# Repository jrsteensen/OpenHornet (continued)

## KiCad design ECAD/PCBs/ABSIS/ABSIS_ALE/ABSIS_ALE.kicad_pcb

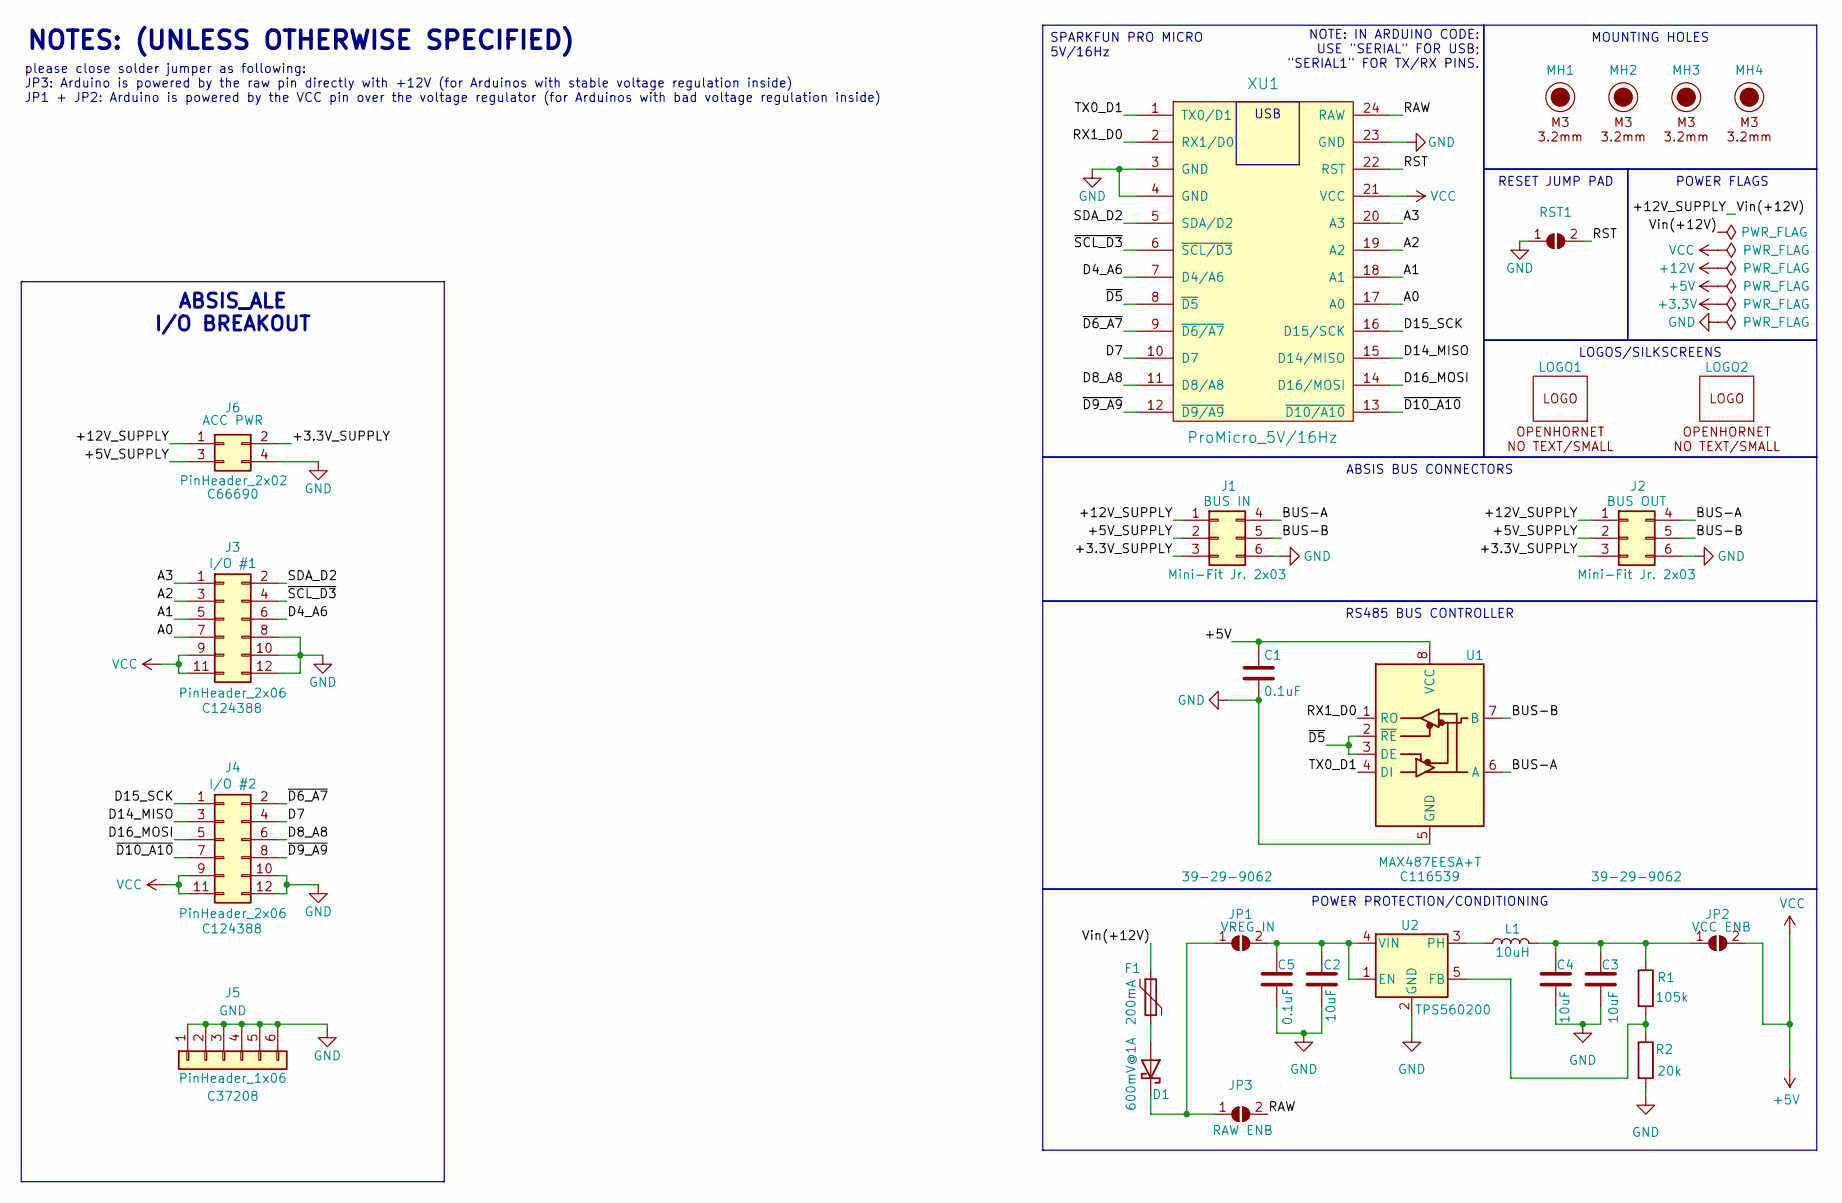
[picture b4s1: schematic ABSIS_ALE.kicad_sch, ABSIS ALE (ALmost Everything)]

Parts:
C1: 0.1uF; C_0805_2012Metric; Manufacturer PN CC0805KRX7R9BB104; LCSC C14663
C2, C3: 10uF; C_0805_2012Metric; Manufacturer PN CL21A106KAYNNNE; LCSC C15850
C4: 10uF; C_0805_2012Metric; Manufacturer PN CC0603KRX5R6BB105; LCSC C15850
C5: 0.1uF; C_0805_2012Metric; Manufacturer PN CC0603KRX7R9BB104; LCSC C14663
D1: 600mV@1A; D_SOD-323_HandSoldering; Manufacturer PN 1N5819WS; LCSC C191023
F1: 200mA; Fuse_0805_2012Metric; Manufacturer PN 0805L020/15XR; LCSC C7472558
J1, J2: Mini-Fit Jr. 2x03; Molex_Mini-Fit_Jr_5566-06A2_2x03_P4.20mm_Vertical; Manufacturer PN 39-29-9062; LCSC C505177
J3, J4: PinHeader_2x06; PinHeader_2x06_P2.54mm_Vertical; Manufacturer PN B-2100S12P-B110; LCSC C124388
J5: PinHeader_1x06; PinHeader_1x06_P2.54mm_Vertical; Manufacturer PN PH1-06-UA; LCSC C37208
J6: PinHeader_2x02; PinHeader_2x02_P2.54mm_Vertical; Manufacturer PN C66690; LCSC C66690
JP1: VREG IN; SolderJumper-2_P1.3mm_Open_RoundedPad1.0x1.5mm
JP2: VCC ENB; SolderJumper-2_P1.3mm_Open_RoundedPad1.0x1.5mm
JP3: RAW ENB; SolderJumper-2_P1.3mm_Open_RoundedPad1.0x1.5mm
L1: 10uH; L_0603_1608Metric; LCSC C86083
LOGO1, LOGO2: LOGO; LOGO_OH_NoText_Small
MH1, MH2, MH3, MH4: M3 / 3.2mm; MountingHole_3.2mm_M3_DIN965
R1: 105k; R_0603_1608Metric; LCSC C141685
R2: 20k; R_0603_1608Metric; LCSC C105575
RST1: RST; SolderJumper-2_P1.3mm_Open_RoundedPad1.0x1.5mm
U1: MAX487EESA+T; SOIC-8_3.9x4.9mm_P1.27mm; Manufacturer PN MAX487EESA+T; LCSC C116539
U2: TPS560200; SOT-23-5; LCSC C83671
XU1: ProMicro_5V/16Hz; DIP-24_W15.24mm_Socket; Manufacturer PN Pro Micro - 5V/16MHz

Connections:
+5V: C1.1, J3.9, J3.11, J4.9, J4.11, JP2.2 (B), U1.8 (VCC), XU1.21 (VCC)
/+3.3V_SUPPLY: J1.3, J2.3, J6.2
/+5V_SUPPLY: J1.2, J2.2, J6.3
/+12V_SUPPLY: F1.1, J1.1, J2.1, J6.1
/A0: J3.7, XU1.17 (A0)
/A1: J3.5, XU1.18 (A1)
/A2: J3.3, XU1.19 (A2)
/A3: J3.1, XU1.20 (A3)
/BUS-A: J1.4, J2.4, U1.6 (A)
/BUS-B: J1.5, J2.5, U1.7 (B)
/D4_A6: J3.6, XU1.7 (D4/A6)
/D7: J4.4, XU1.10 (D7)
/D8_A8: J4.6, XU1.11 (D8/A8)
/D14_MISO: J4.3, XU1.15 (D14/MISO)
/D15_SCK: J4.1, XU1.16 (D15/SCK)
/D16_MOSI: J4.5, XU1.14 (D16/MOSI)
/RAW: JP3.2 (B), XU1.24 (RAW)
/RST: RST1.2 (B), XU1.22 (RST)
/RX1_D0: U1.1 (RO), XU1.2 (RX1/D0)
/SDA_D2: J3.2, XU1.5 (SDA/D2)
/TX0_D1: U1.4 (DI), XU1.1 (TX0/D1)
/~D5: U1.2 (~RE), U1.3 (DE), XU1.8 (~D5)
/~D6_A7: J4.2, XU1.9 (~D6/A7)
/~D9_A9: J4.8, XU1.12 (~D9/A9)
/~D10_A10: J4.7, XU1.13 (~D10/A10)
/~SCL_D3: J3.4, XU1.6 (~SCL/D3)
GND: C1.2, C2.2, C3.2, C4.2, C5.2, J1.6, J2.6, J3.8, J3.10, J3.12, J4.10, J4.12, J5.1, J5.2, J5.3, J5.4, J5.5, J5.6, J6.4, R2.2, RST1.1 (A), U1.5 (GND), U2.2 (GND), XU1.3 (GND), XU1.4 (GND), XU1.23 (GND)
unnamed: D1.2 (A), F1.2
unnamed: D1.1 (K), JP1.1 (A), JP3.1 (A)
unnamed: C2.1, C5.1, JP1.2 (B), U2.1 (EN), U2.4 (VIN)
unnamed: C3.1, C4.1, JP2.1 (A), L1.2, R1.1
unnamed: R1.2, R2.1, U2.5 (FB)
unnamed: L1.1, U2.3 (PH)

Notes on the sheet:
NOTES: (UNLESS OTHERWISE SPECIFIED)
NOTE: IN ARDUINO CODE: USE "SERIAL" FOR USB; "SERIAL1" FOR TX/RX PINS.
please close solder jumper as following: JP3: Arduino is powered by the raw pin directly with +12V (for Arduinos with stable voltage regulation inside) JP1 + JP2: Arduino is powered by the VCC pin over the voltage regulator (for Arduinos with bad voltage regulation inside)
SPARKFUN PRO MICRO 5V/16Hz
LOGOS/SILKSCREENS
USB
RS485 BUS CONTROLLER
POWER PROTECTION/CONDITIONING
POWER FLAGS
ABSIS_ALE I/O BREAKOUT
MOUNTING HOLES
RESET JUMP PAD
ABSIS BUS CONNECTORS

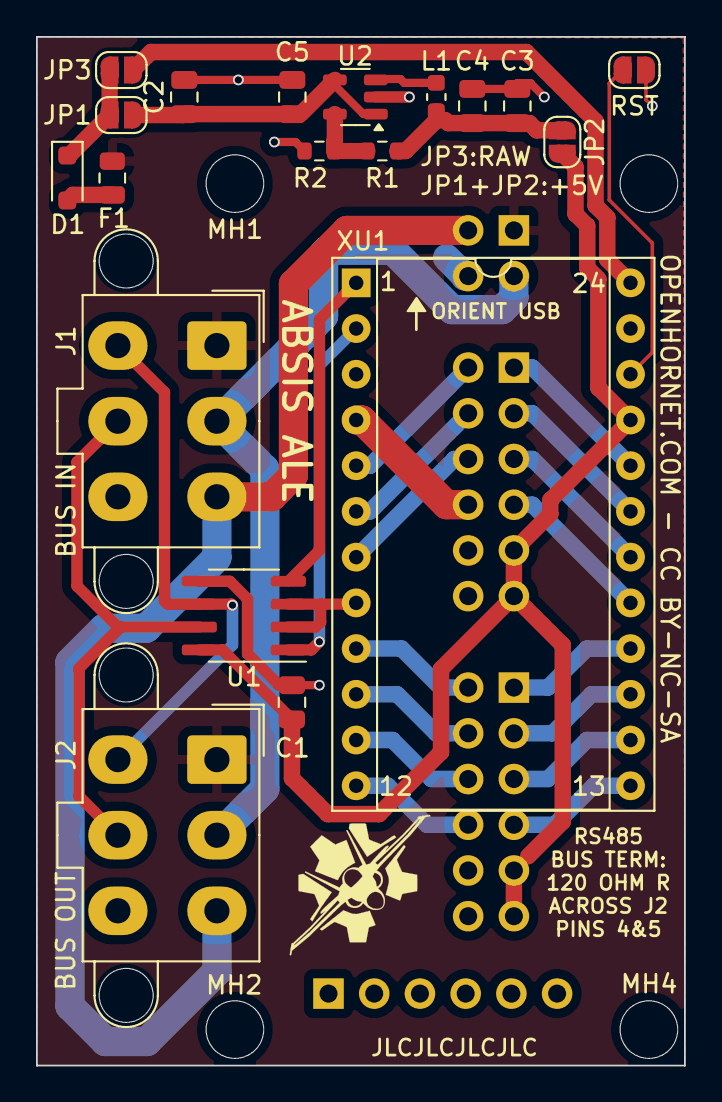
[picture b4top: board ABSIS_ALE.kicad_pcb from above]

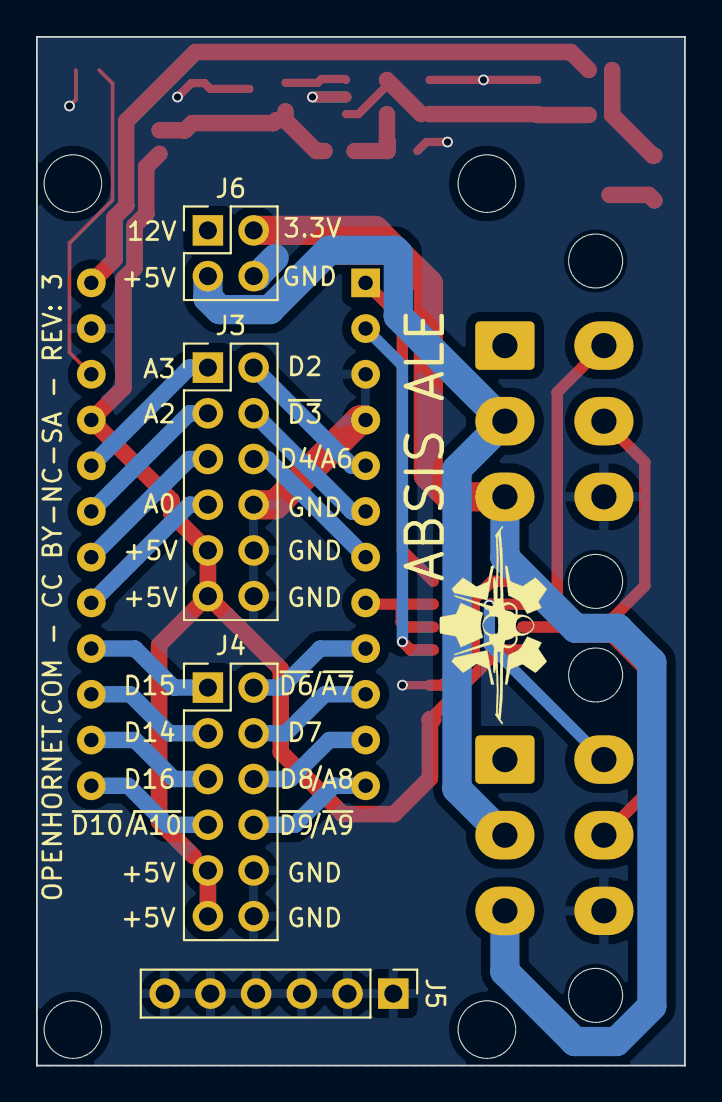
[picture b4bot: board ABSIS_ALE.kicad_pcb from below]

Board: 2 copper layers, 36.0 x 57.2 mm, 29 parts (5 on the bottom side), 33 nets.

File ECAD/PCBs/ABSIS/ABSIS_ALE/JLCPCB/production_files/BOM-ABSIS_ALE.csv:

"Reference","Value","Datasheet","Footprint","Qty","DNP","LCSC"
"C1,C5","0.1uF","https://datasheet.lcsc.com/szlcsc/YAGEO-CChttps://datasheet.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","OH_Footprints:C_0805_2012Metric","2","","C5120075"
"C2,C3,C4","10uF","https://datasheet.lcsc.com/szlcsc/Samsung-Electro-Mechanics-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","OH_Footprints:C_0805_2012Metric","3","","C15850"
"D1","600mV@1A","https://www.lcsc.com/datasheet/lcsc_datasheet_2204281430_Gua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","Diode_SMD:D_SOD-323_HandSoldering","1","","C191023"
"F1","200mA","https://wmsc.lcsc.com/wmsc/upload/file/pdf/v2/lcsc/240103172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","Fuse:Fuse_0805_2012Metric","1","","C7472558"
"J1,J2","Mini-Fit Jr. 2x03","https://datasheet.lcsc.com/lcsc/2005291105_MOLEX-39299062_C5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","OH_Footprints:Molex_Mini-Fit_Jr_5566-06A2_2x03_P4.20mm_Vertical","2","","C505177"
"J3,J4","PinHeader_2x06","https://datasheet.lcsc.com/lcsc/1810241611_Ckmtw-Shenzhen-Ca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","OH_Footprints:PinHeader_2x06_P2.54mm_Vertical","2","","C124388"
"J5","PinHeader_1x06","https://datasheet.lcsc.com/lcsc/1810312320_BOOMELE-Boom-Prec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","OH_Footprints:PinHeader_1x06_P2.54mm_Vertical","1","","C37208"
"J6","PinHeader_2x02","https://jlcpcb.com/partdetail/boomele_boom_Precision_elec-C6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","OH_Footprints:PinHeader_2x02_P2.54mm_Vertical","1","","C66690"
"L1","10uH","https://www.lcsc.com/datasheet/lcsc_datasheet_2410121333_Mur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","Inductor_SMD:L_0603_1608Metric","1","","C86083"
"R1","105k","https://www.lcsc.com/datasheet/C98220.pdf","Resistor_SMD:R_0603_1608Metric","1","","C141685"
"R2","20k","https://www.lcsc.com/datasheet/C98220.pdf","Resistor_SMD:R_0603_1608Metric","1","","C105575"
"U1","MAX487EESA+T","https://datasheet.lcsc.com/szlcsc/Maxim-Integrated-MAX487EES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","OH_Footprints:SOIC-8_3.9x4.9mm_P1.27mm","1","","C116539"
"U2","TPS560200","http://www.ti.com/lit/ds/symlink/tps560200.pdf","Package_TO_SOT_SMD:SOT-23-5","1","","C83671"
"XU1","ProMicro_5V/16Hz","https://cdn.sparkfun.com/datasheets/Dev/Arduino/Boards/ATMeg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","OH_Footprints:DIP-24_W15.24mm_Socket","1","",""

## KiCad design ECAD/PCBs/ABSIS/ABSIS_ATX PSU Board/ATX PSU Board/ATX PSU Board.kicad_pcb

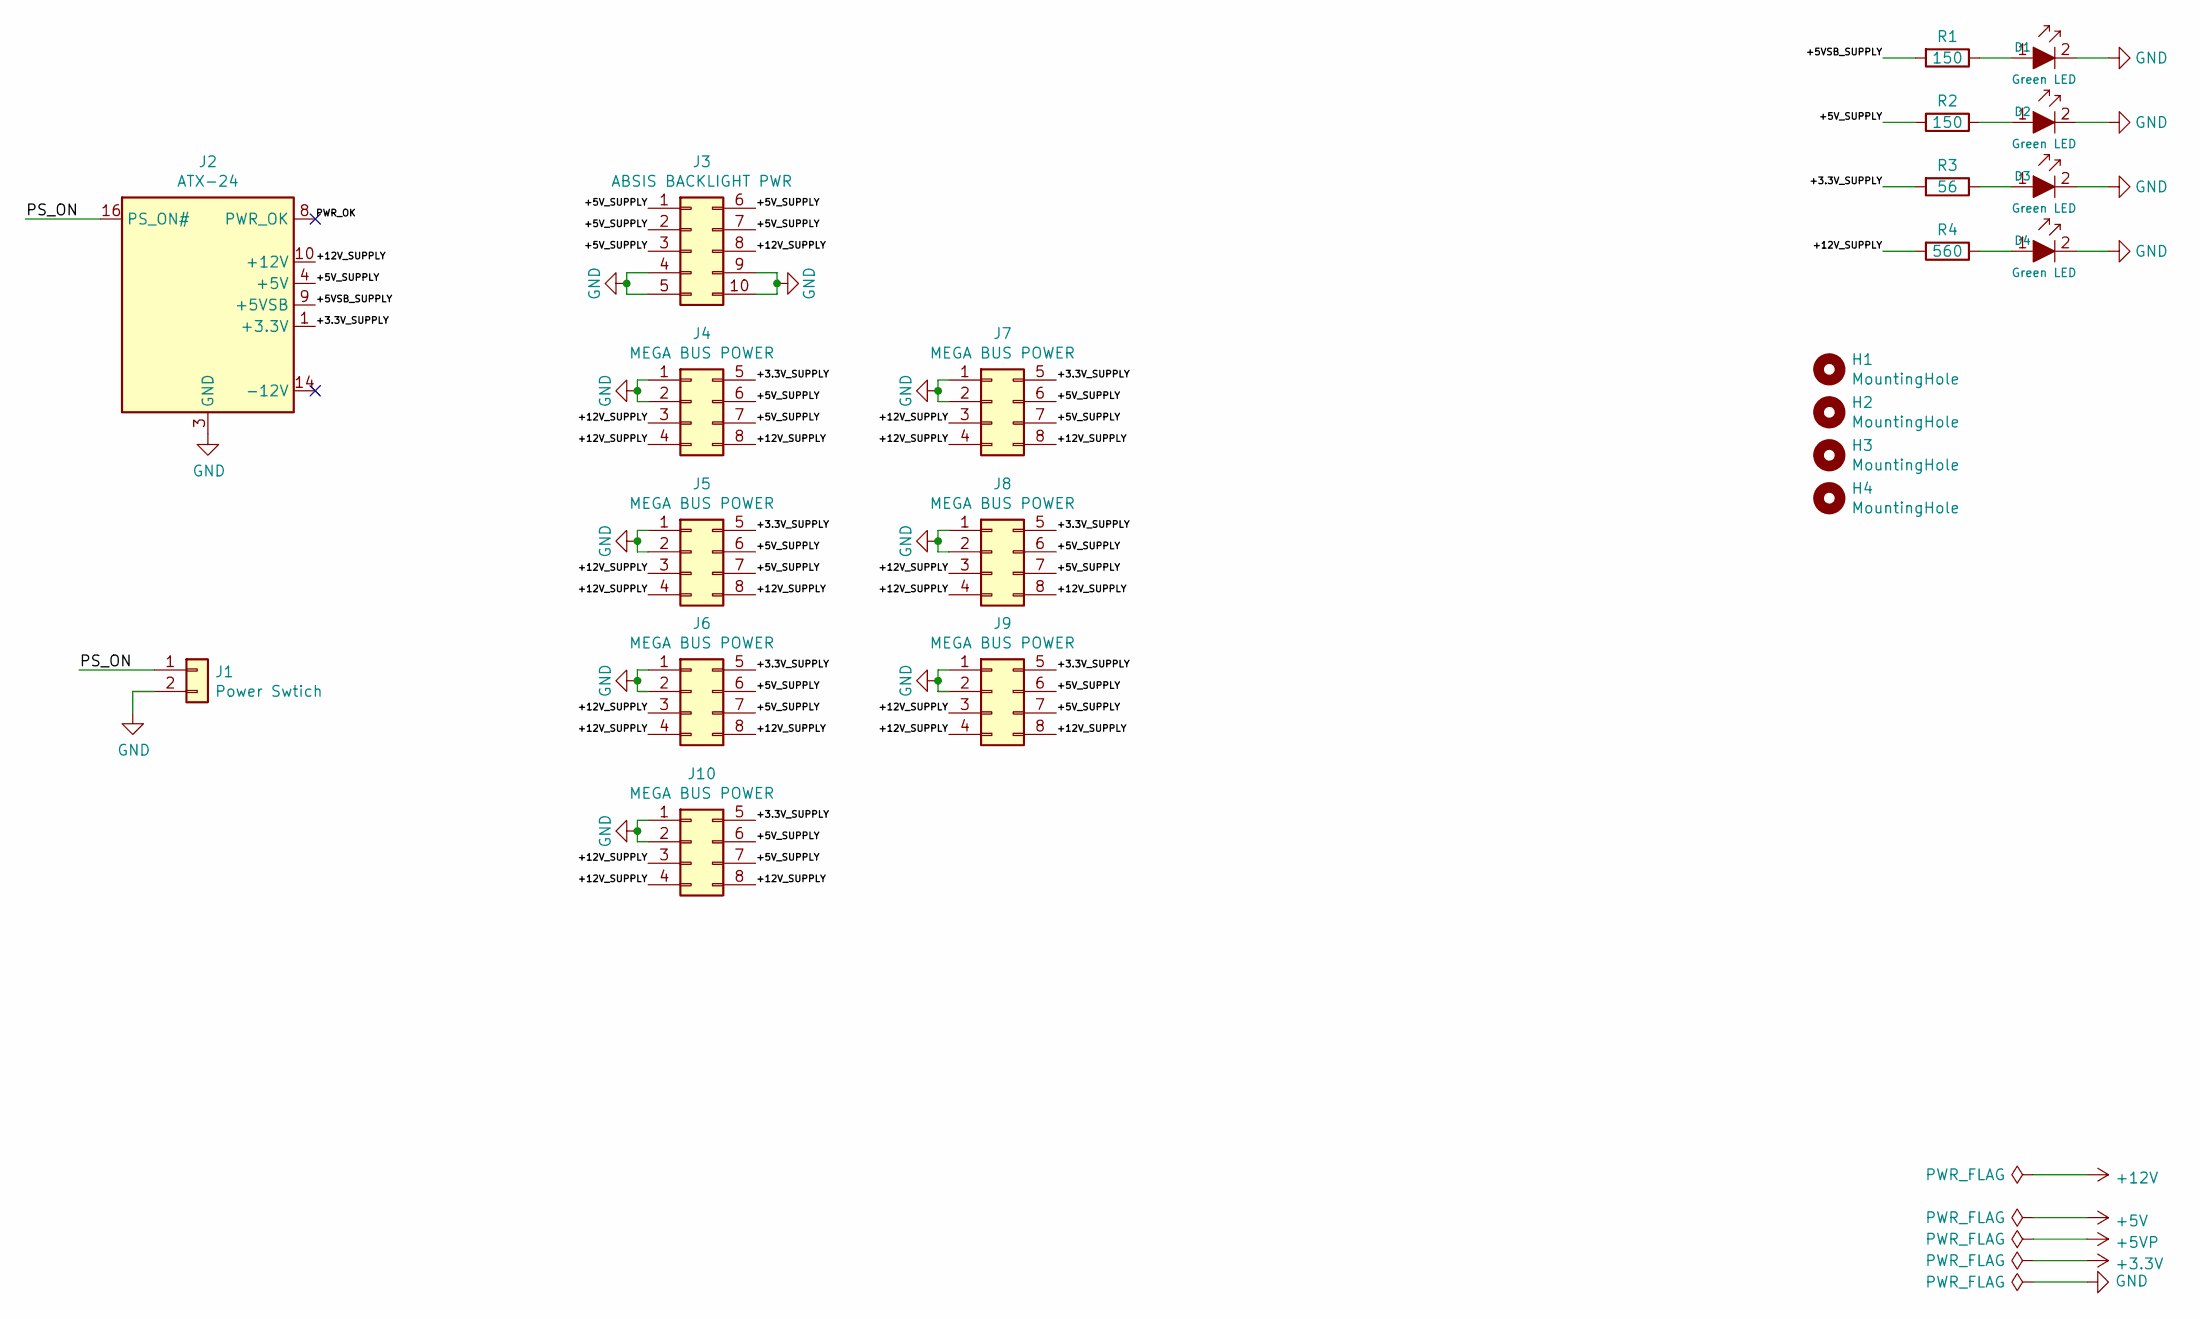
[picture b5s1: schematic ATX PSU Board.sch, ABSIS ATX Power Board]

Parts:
D1, D2, D3, D4: Green LED; LED_0805_2012Metric_Pad1.15x1.40mm_HandSolder; MPN LG R971-KN-1; Digi-Key_PN 475-1410-1-ND
H1, H2, H3, H4: MountingHole; Arduino_1pin
J1: Power Swtich; Molex_Micro-Fit_3.0_43045-0212_2x01_P3.00mm_Vertical
J2: ATX-24; Molex_Mini-Fit_Jr_5566-24A2_2x12_P4.20mm_Vertical
J3: ABSIS BACKLIGHT PWR; Molex_Mini-Fit_Jr_5566-10A2_2x05_P4.20mm_Vertical
J4, J5, J6, J7, J8, J9, J10: MEGA BUS POWER; Molex_Mini-Fit_Jr_5566-08A2_2x04_P4.20mm_Vertical
R1, R2: 150; R_0805_2012Metric_Pad1.20x1.40mm_HandSolder
R3: 56; R_0805_2012Metric_Pad1.20x1.40mm_HandSolder
R4: 560; R_0805_2012Metric_Pad1.20x1.40mm_HandSolder

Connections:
/+3.3V_SUPPLY: J2.1 (+3.3V), J2.2 (+3.3V), J2.12 (+3.3V), J2.13 (+3.3V), J4.5, J5.5, J6.5, J7.5, J8.5, J9.5, J10.5, R3.2
/+5VSB_SUPPLY: J2.9 (+5VSB), R1.2
/+5V_SUPPLY: J2.4 (+5V), J2.6 (+5V), J2.21 (+5V), J2.22 (+5V), J2.23 (+5V), J3.1, J3.2, J3.3, J3.6, J3.7, J4.6, J4.7, J5.6, J5.7, J6.6, J6.7, J7.6, J7.7, J8.6, J8.7, J9.6, J9.7, J10.6, J10.7, R2.2
/+12V_SUPPLY: J2.10 (+12V), J2.11 (+12V), J3.8, J4.3, J4.4, J4.8, J5.3, J5.4, J5.8, J6.3, J6.4, J6.8, J7.3, J7.4, J7.8, J8.3, J8.4, J8.8, J9.3, J9.4, J9.8, J10.3, J10.4, J10.8, R4.2
/PS_ON: J1.1, J2.16 (PS_ON#)
/PWR_OK: J2.8 (PWR_OK)
GND: D1.2, D2.2, D3.2, D4.2, J1.2, J2.3 (GND), J2.5 (GND), J2.7 (GND), J2.15 (GND), J2.17 (GND), J2.18 (GND), J2.19 (GND), J2.24 (GND), J3.4, J3.5, J3.9, J3.10, J4.1, J4.2, J5.1, J5.2, J6.1, J6.2, J7.1, J7.2, J8.1, J8.2, J9.1, J9.2, J10.1, J10.2
unnamed: D1.1, R1.1
unnamed: D2.1, R2.1
unnamed: D3.1, R3.1
unnamed: D4.1, R4.1

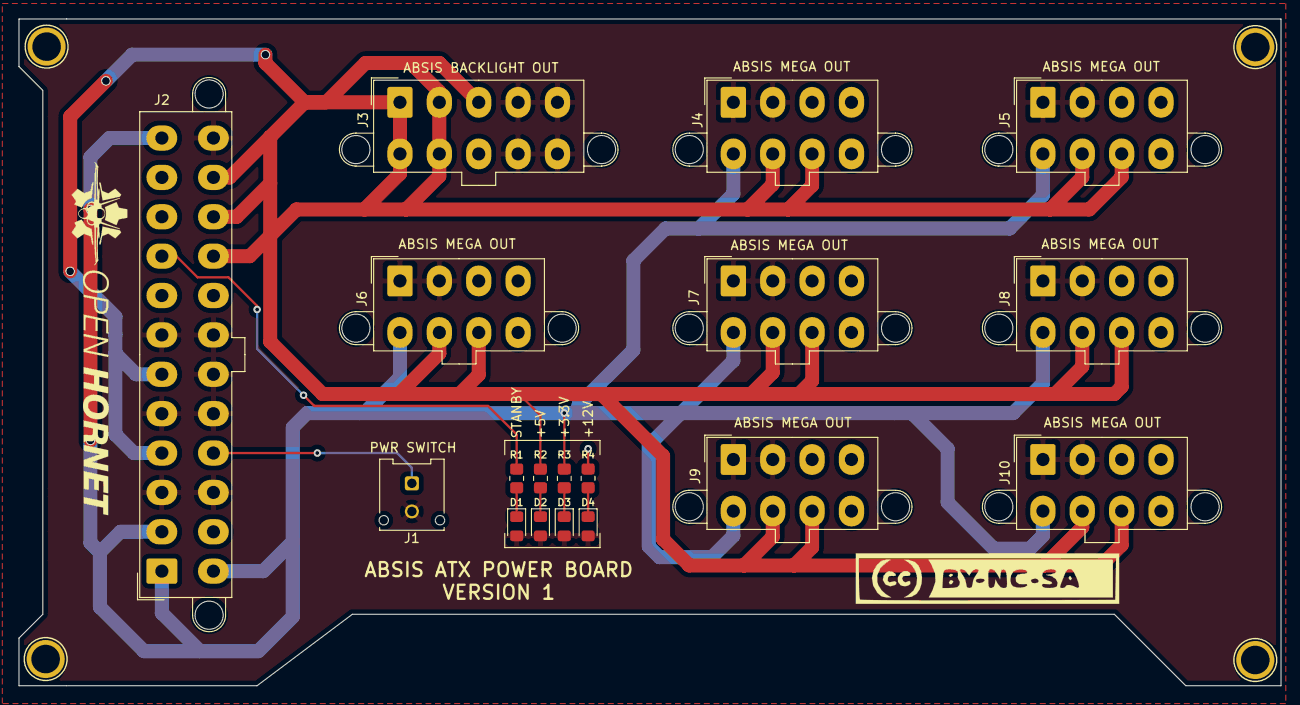
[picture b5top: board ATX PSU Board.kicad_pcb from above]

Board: 2 copper layers, 134.6 x 71.1 mm, 22 parts (0 on the bottom side), 10 nets.

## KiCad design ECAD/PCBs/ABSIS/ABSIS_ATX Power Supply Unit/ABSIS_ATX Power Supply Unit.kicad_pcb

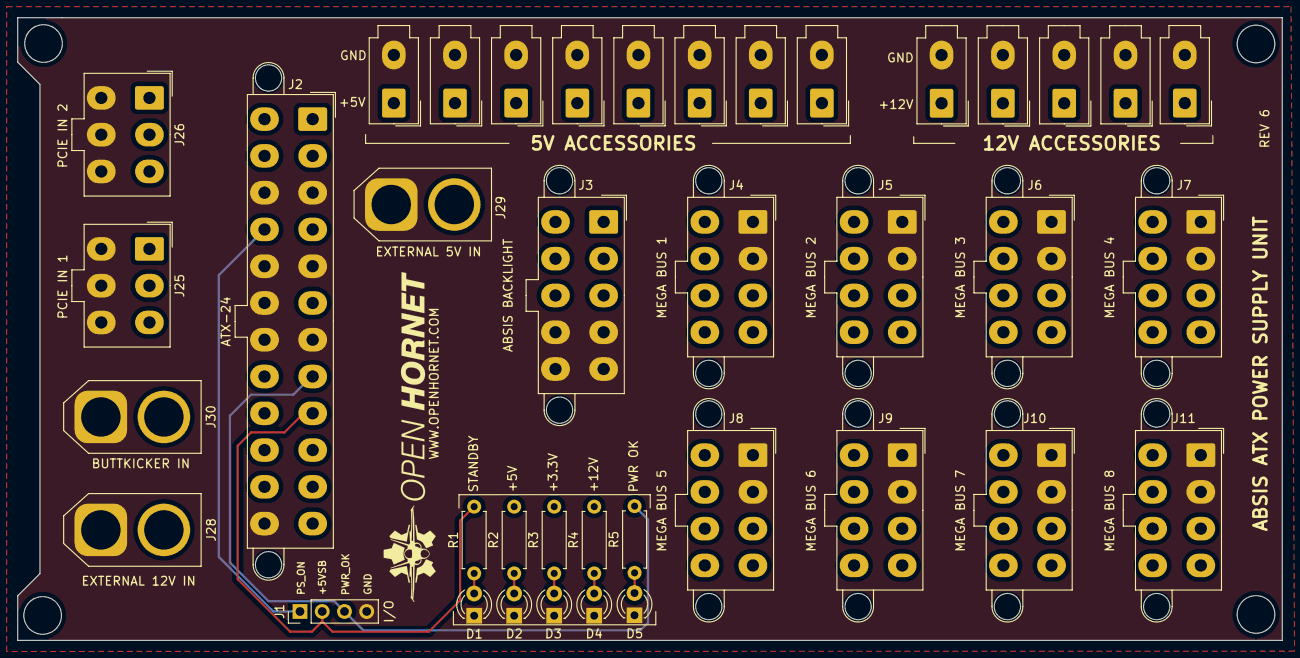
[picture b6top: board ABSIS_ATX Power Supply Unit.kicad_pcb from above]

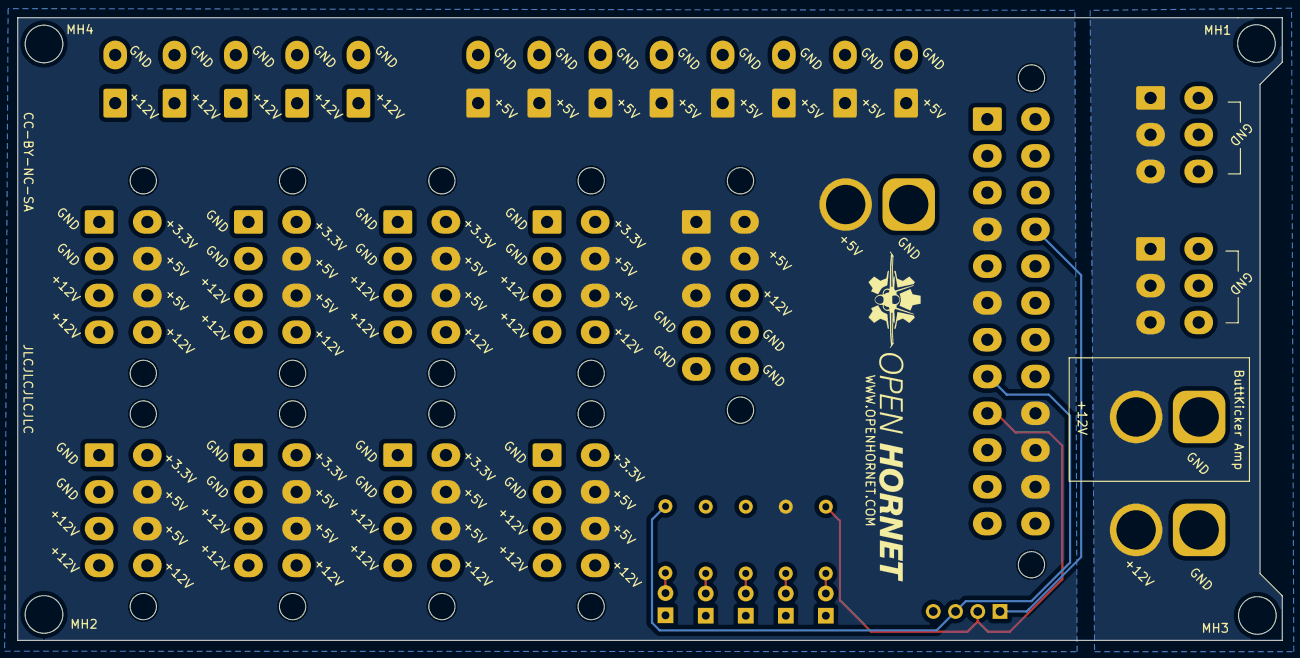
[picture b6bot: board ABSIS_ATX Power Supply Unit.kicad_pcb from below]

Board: 4 copper layers, 144.4 x 71.1 mm, 45 parts (5 on the bottom side), 12 nets.

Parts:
D1: Blue; LED_D3.0mm
D2, D3, D4, D5: Green; LED_D3.0mm
J1: PinHeader_1x04; PinHeader_1x04_P2.54mm_Vertical
J2: Molex_Mini-Fit_Jr._2x12; Molex_Mini-Fit_Jr_5566-24A2_2x12_P4.20mm_Vertical
J3: Molex_Mini-fit_Jr._2x05; Molex_Mini-Fit_Jr_5566-10A2_2x05_P4.20mm_Vertical
J4, J5, J6, J7, J8, J9, J10, J11: Molex_Mini-Fit_Jr._2x04; Molex_Mini-Fit_Jr_5566-08A2_2x04_P4.20mm_Vertical
J12, J13, J14, J15, J16, J17, J18, J19, J20, J21, J22, J23, J24: Molex_Mini-Fit_Jr._1x02; Molex_Mini-Fit_Jr_5566-02A_2x01_P4.20mm_Vertical
J25, J26: Mini-Fit Jr. 2x03; Molex_Mini-Fit_Jr_5566-06A_2x03_P4.20mm_Vertical
J28, J29: AMASS_XT60_M; AMASS_XT60-M_1x02_P7.20mm_Vertical
J30: AMASS_XT60_F; AMASS_XT60-F_1x02_P7.20mm_Vertical
LOGO1, LOGO2: LOGO; LOGO_OH_Text_Small
MH1, MH2, MH3, MH4: 6x32 / 4mm; MountingHole_6-32_PHS
R1, R2, R5: 150; R_Axial_DIN0207_L6.3mm_D2.5mm_P7.62mm_Horizontal
R3: 56; R_Axial_DIN0207_L6.3mm_D2.5mm_P7.62mm_Horizontal
R4: 560; R_Axial_DIN0207_L6.3mm_D2.5mm_P7.62mm_Horizontal

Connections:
/+3.3V_SUPPLY: J2.1 (+3.3V), J2.2 (+3.3V), J2.12 (+3.3V), J2.13 (+3.3V), J4.5, J5.5, J6.5, J7.5, J8.5, J9.5, J10.5, J11.5, R3.2
/+5VSB_SUPPLY: J1.2, J2.9 (+5VSB), R1.2
/+5V_SUPPLY: J2.4 (+5V), J2.6 (+5V), J2.21 (+5V), J2.22 (+5V), J2.23 (+5V), J3.1, J3.2, J3.3, J3.6, J3.7, J4.6, J4.7, J5.6, J5.7, J6.6, J6.7, J7.6, J7.7, J8.6, J8.7, J9.6, J9.7, J10.6, J10.7, J11.6, J11.7, J12.1, J13.1, J14.1, J15.1, J16.1, J17.1, J18.1, J19.1, J29.2, R2.2
/+12V_SUPPLY: J2.10 (+12V), J2.11 (+12V), J3.8, J4.3, J4.4, J4.8, J5.3, J5.4, J5.8, J6.3, J6.4, J6.8, J7.3, J7.4, J7.8, J8.3, J8.4, J8.8, J9.3, J9.4, J9.8, J10.3, J10.4, J10.8, J11.3, J11.4, J11.8, J20.1, J21.1, J22.1, J23.1, J24.1, J25.1, J25.2, J25.3, J26.1, J26.2, J26.3, J28.2, J30.2, R4.2
/PS_ON: J1.1, J2.16 (PS_ON#)
/PWR_OK: J1.3, J2.8 (PWR_OK), R5.2
GND: D1.1 (K), D2.1 (K), D3.1 (K), D4.1 (K), D5.1 (K), J1.4, J2.3 (GND), J2.5 (GND), J2.7 (GND), J2.15 (GND), J2.17 (GND), J2.18 (GND), J2.19 (GND), J2.24 (GND), J3.4, J3.5, J3.9, J3.10, J4.1, J4.2, J5.1, J5.2, J6.1, J6.2, J7.1, J7.2, J8.1, J8.2, J9.1, J9.2, J10.1, J10.2, J11.1, J11.2, J12.2, J13.2, J14.2, J15.2, J16.2, J17.2, J18.2, J19.2, J20.2, J21.2, J22.2, J23.2, J24.2, J25.4, J25.5, J25.6, J26.4, J26.5, J26.6, J28.1, J29.1, J30.1
unnamed: D1.2 (A), R1.1
unnamed: D2.2 (A), R2.1
unnamed: D3.2 (A), R3.1
unnamed: D4.2 (A), R4.1
unnamed: D5.2 (A), R5.1
